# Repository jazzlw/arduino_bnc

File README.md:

# BNC Shield for Arduino

<!--  -->

*Now orderable from my [Etsy store](https://www.etsy.com/listing/1844833694/bnc-shield-for-arduino)*

The BNC Shield for Arduino is a very simple way to reliably connect an Arduino to one or more BNC
cables.

Especially in science, it is very common to use an Arduino to trigger a camera or behavioral system or LED from a computer, and most of the commercially available devices that are triggered have BNC input connections. This often leads to flaky and problematic ways of connecting the Arduino to the BNC cable, and thus experimental setups that are delicate.  This simple shield aims to address this problem and give a reliable solution, without any complicated parts or difficult soldering.

## Features

Up to ten BNC ports attached to different pins on the Arduino.  Five of these pins (3, 5, 6, 9, 10) can be used for digital input our output, and all are PWM capable.  The other five (A0 - A4) can be used for reading analog input voltages, as well as also being usable for digital IO.

There is also a prototyping area with 0.1 inch pitch through holes, in case you want to add any extra parts such as sensors or digital to analog  converters (DACs) or similar. Two of the BNC ports (3 and A4) have jumpers so that they can be easily attached to something in the prototyping area, such as a DAC, instead of to their Arduino pins. See [adding an analog voltage output](docs/adding_analog_out.md) for details and instructions.

## Getting one

To make it super easy to get one of these, I've just put some up on an [Etsy store](https://www.etsy.com/listing/1526648413/arduino-bnc-shield).  You can get just the board, made matte black with high quality immersion gold coating, as shown in the pictures above. You can also get the other parts there, and you can also order it pre-soldered if you want.

With a little more effort, the BNC Shield for Arduino can be ordered easily and cheaply from any PCB board house (such as [pcbway](pcbway.com), [jlcpcb](jlcpcb.com), etc)  using the zipped gerber files in `bnc_shield_pcb/bnc_shield_gerbers.zip`. You'll need to input the size of the desired board, which is 3.6 inches by 3.6 inches. Many board houses have a deal for 5 PCBs of this size for under $10 plus shipping (although without the black solder mask or gold coating mentioned above). The only other parts you need are an Arduino Uno, some BNC jacks, and some header to connect the shield to the Arduino. The whole thing can then be easily and quickly assembled even by someone with no soldering experience using only a soldering iron and solder.

## Build Instructions

The BNC Shield for Arduino was designed to be super easy and quick to assemble, even without any experience! For most use cases, all you need to do is solder some [0.1 inch male header](https://www.digikey.com/en/products/detail/sullins-connector-solutions/PRPC040SAAN-RC/2775214) onto the shield to connect it to the Arduino, and some [BNC Jacks](https://www.digikey.com/en/products/detail/sullins-connector-solutions/PRPC040SAAN-RC/2775214) to connect your BNC cables. For the header, it can be helpful to start by putting the long side of the headers into an Arduino to hold them, and then putting the shield on top to solder it. If you've never soldered before, don't worry, it's very learnable! There are many great YouTube videos and other guides on the internet to show you how, such as [this one from AdaFruit.](https://learn.adafruit.com/adafruit-guide-excellent-soldering/preparation)

Now you're ready to load some code on the Arduino with the [Arduino IDE](https://www.arduino.cc/en/software) and try it out! Check out the things in the `examples` folder for ideas.

## Case
<!--  -->

There are files for a 3D printed case that fits an Arduino Uno with the BNC Shield for Arduino in the folder [arduino_bnc_case](arduino_bnc_case).  You can either print the top lid using the `.stl` file, or laser cut one out of 1/8 inch acrylic using the `.svg` file, as shown to the right. Tap the three standoffs in the bottom of the case to #4-40 using a [tap](https://www.mcmaster.com/25995A125/), and use [1.5 inch long #4-40 screws](https://www.mcmaster.com/92949A120/) to attach the lid and hold the Arduino BNC down.

## Getting one

To make it super easy to get one of these, I've just put some up on an [Etsy store](https://www.etsy.com/listing/1526648413/arduino-bnc-shield).  You can get just the board, made matte black with high quality immersion gold coating, as shown in the pictures above. You can also get the other parts there, and you can order it pre-soldered if you want.

The BNC Shield for Arduino can be ordered easily and cheaply from any PCB board house (such as [pcbway](pcbway.com), [jlcpcb](jlcpcb.com), etc)  using the zipped gerber files in `bnc_shield_pcb/bnc_shield_gerbers.zip`. You'll need to input the size of the desired board, which is 3.6 inches by 3.6 inches. Many board houses have a deal for 5 PCBs of this size for under $10 plus shipping. The only other parts you need are an Arduino Uno, some BNC jacks, and some header to connect the shield to the Arduino. The whole thing can then be easily and quickly assembled even by someone with no soldering experience using only a soldering iron and solder.

### Required parts

You will need a few parts in order to complete the BNC Shield for Arduino, as shown below. For the BNC Jacks, you don't need to install all 10 if you won't be using all 10 channels, just the ones you plan to use.

|Part|Quantity|Part Number|Supplier Link|
|---|---|---|---|
|BNC Shield for Arduino PCB| 1 | N/A | See above
|Arduino Uno|1|A000066 | <https://www.digikey.com/reference-designs/en/open-source-mcu-platforms/2481>|
|BNC Jack|1-10|0731375003 | <https://www.digikey.com/en/products/detail/molex/0731375003/1465136>|
|Male 0.1 in Header|2|PRPC040SAAN-RC | <https://www.digikey.com/en/products/detail/sullins-connector-solutions/PRPC040SAAN-RC/2775214>

### Optional Parts

|Part|Quantity|Part Number|Supplier Link|
|---|---|---|---|
|Reset Button|1| 450-1650-ND |  <https://www.digikey.com/en/products/detail/te-connectivity-alcoswitch-switches/1825910-6/1632536>|
|Shield Stacking Header|1 set| 85|<https://www.adafruit.com/product/85> |
|[Digital to Analog Converter  (DAC)](docs/adding_analog_out.md) | 1| 935 |  <https://www.adafruit.com/product/935>
|4-40 tap for case | 1 | 25995A125 | <https://www.mcmaster.com/25995A125> |
| 1.5 inch long #4-40 screws for case| 3  | 92949A120 | <https://www.mcmaster.com/92949A120>|

<br />This work is licensed under a <a rel="license" href="http://creativecommons.org/licenses/by-sa/4.0/">Creative Commons Attribution-ShareAlike 4.0 International License</a>.

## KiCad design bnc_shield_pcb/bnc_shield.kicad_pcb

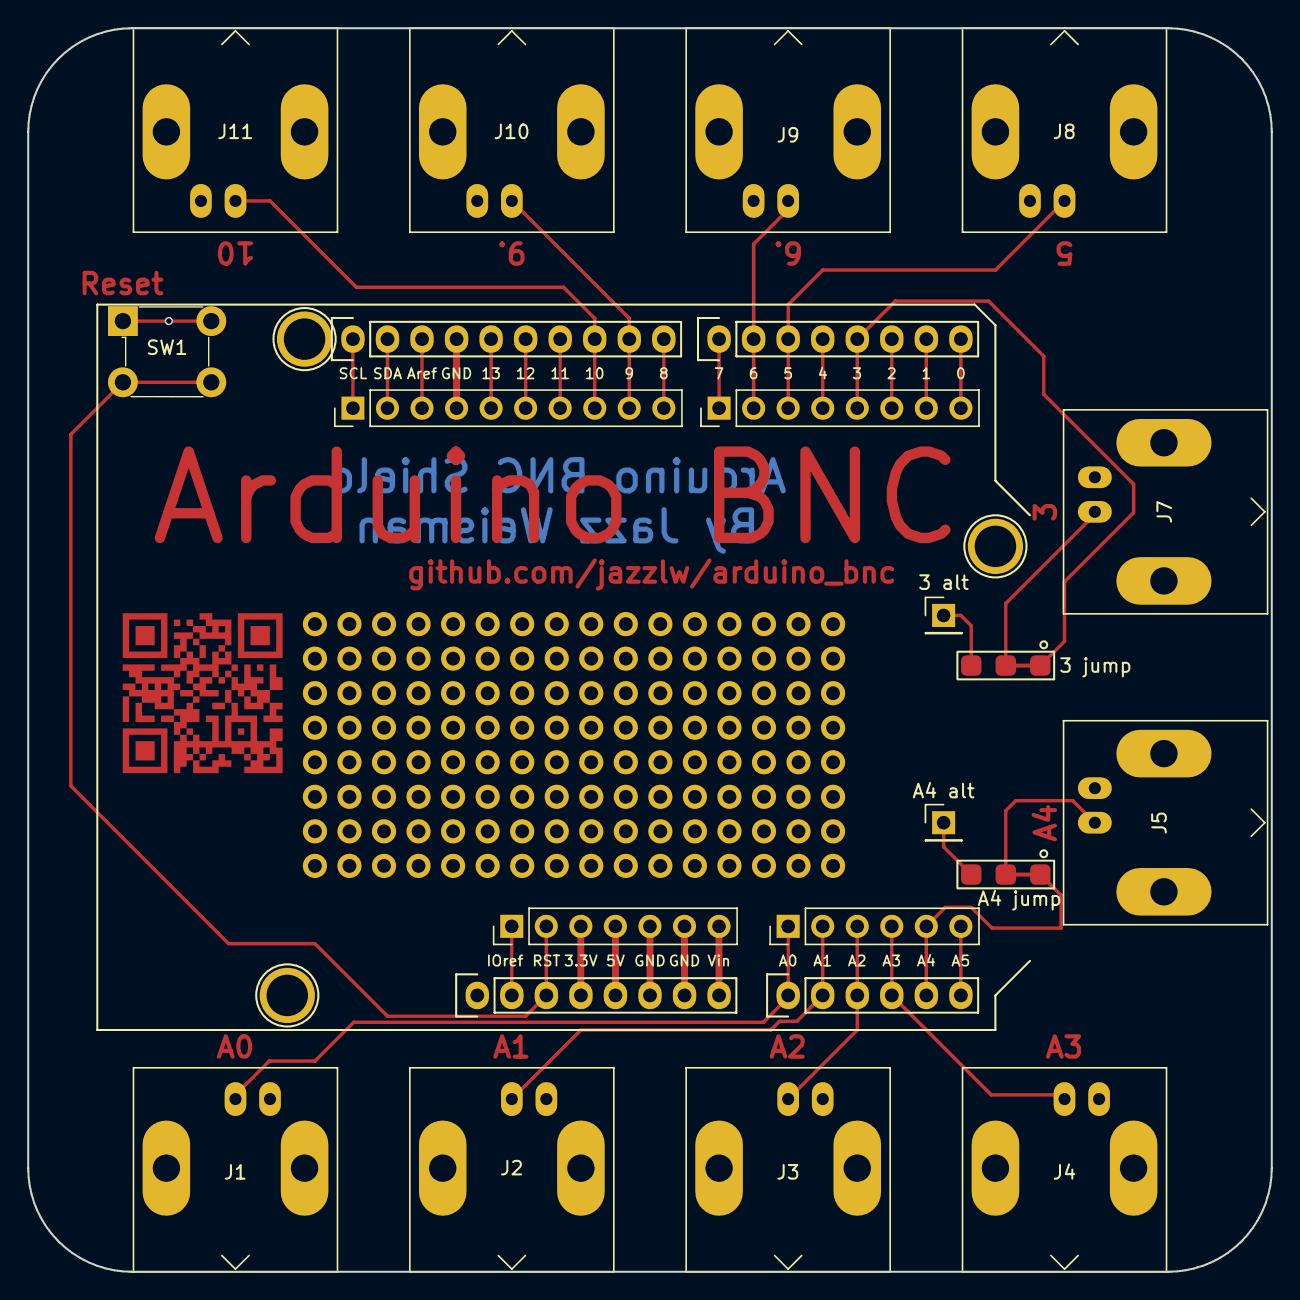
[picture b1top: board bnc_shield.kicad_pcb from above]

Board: 2 copper layers, 91.4 x 91.4 mm, 26 parts (0 on the bottom side), 31 nets.

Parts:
3 alt: Conn_01x01_Male; PinHeader_1x01_P2.54mm_Vertical
3 jump: jumper; SolderJumper-3-P2.54mm_Bridged12
A4 alt: Conn_01x01_Male; PinHeader_1x01_P2.54mm_Vertical
A4 jump: jumper; SolderJumper-3-P2.54mm_Bridged12
J1, J2, J3, J4, J5, J7, J8, J9, J10, J11: Conn_Coaxial; BNC_Amphenol_B6252HB-NPP3G-50_Horizontal
J6: Conn_01x07_Male; PinHeader_1x07_P2.54mm_Vertical
J12: Conn_01x06_Male; PinHeader_1x06_P2.54mm_Vertical
J13: Conn_01x10_Male; PinHeader_1x10_P2.54mm_Vertical
J14: Conn_01x08_Male; PinHeader_1x08_P2.54mm_Vertical
P1: Power; Socket_Strip_Arduino_1x08
P2: Analog; Socket_Strip_Arduino_1x06
P3: Digital; Socket_Strip_Arduino_1x10
P4: Digital; Socket_Strip_Arduino_1x08
P5, P7, P8: CONN_01X01; Arduino_1pin
SW1: SW_MEC_5E; Switch_Tactile_THT_6x6mm

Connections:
+3V3: J6.3, P1.4
+5V: J6.4, P1.5
/0(Rx): J14.8, P4.8
/1(Tx): J14.7, P4.7
/2: J14.6, P4.6
/3(**): 3 jump.1 (A), J14.5, P4.5
/4: J14.4, P4.4
/5(**): J8.1 (In), J14.3, P4.3
/6(**): J9.1 (In), J14.2, P4.2
/7: J14.1, P4.1
/8: J13.10, P3.10
/9(**): J10.1 (In), J13.9, P3.9
/10(**/SS): J11.1 (In), J13.8, P3.8
/11(**/MOSI): J13.7, P3.7
/12(MISO): J13.6, P3.6
/13(SCK): J13.5, P3.5
/A0: J1.1 (In), J12.1, P2.1
/A1: J2.1 (In), J12.2, P2.2
/A2: J3.1 (In), J12.3, P2.3
/A3: J4.1 (In), J12.4, P2.4
/A4(SDA): A4 jump.1 (A), J12.5, J13.2, P2.5, P3.2
/A5(SCL): J12.6, J13.1, P2.6, P3.1
/AREF: J13.3, P3.3
/IOREF: J6.1, P1.2
/Reset: J6.2, P1.3, SW1.3 (K), SW1.4 (A)
/Vin: J6.7, P1.8
GND: J1.2 (Ext), J2.2 (Ext), J3.2 (Ext), J4.2 (Ext), J5.2 (Ext), J6.5, J6.6, J7.2 (Ext), J8.2 (Ext), J9.2 (Ext), J10.2 (Ext), J11.2 (Ext), J13.4, P1.6, P1.7, P3.4, SW1.1, SW1.2
unnamed: A4 jump.2 (C), J5.1 (In)
unnamed: 3 jump.2 (C), J7.1 (In)
unnamed: A4 alt.1, A4 jump.3 (B)
unnamed: 3 alt.1, 3 jump.3 (B)

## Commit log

2022-09-02 Initial Commit. First boards ordered
2022-09-12 readme updates
2022-09-12 added analog output doc
2022-09-15 added license
2022-11-18 added part quantities
2023-06-13 added board dimensions
2023-07-20 Version 2, as ordered
2023-07-20 updated readme with note about V2 upcoming
2023-10-19 updated with case and new version
2024-11-02 added stl of case bottom
2025-01-15 Update README.md to reflect new name
2025-01-15 fixed etsy link
